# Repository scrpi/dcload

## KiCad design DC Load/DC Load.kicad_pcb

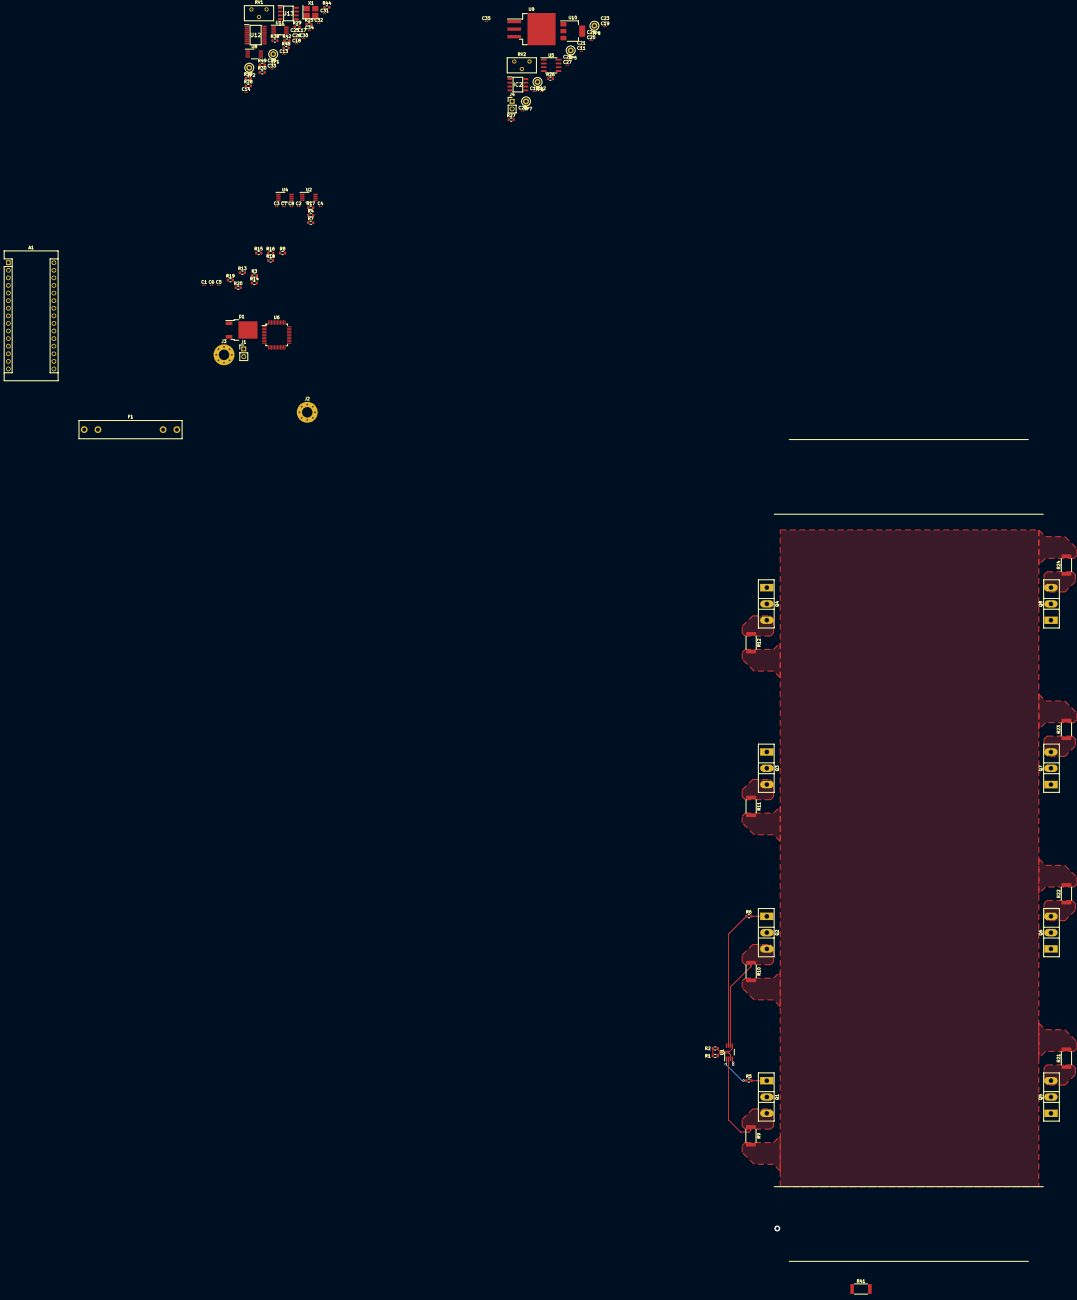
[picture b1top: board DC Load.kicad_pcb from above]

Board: 2 copper layers, 105 parts (0 on the bottom side), 62 nets.

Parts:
A1: Arduino_Nano_v3.x; Arduino_Nano
C1, C3, C5, C7, C10, C17, C20, C21, C26, C32: 1uF; C_0201_0603Metric
C2, C4, C6, C8, C13, C14, C18, C22, C23, C29, C30, C33: 0.1uF; C_0201_0603Metric
C11, C12, C24, C27, C28: 10uF; C_0201_0603Metric
C19: 470uF; C_0201_0603Metric
C25, C34, C35: 10nF; C_0201_0603Metric
C31: 0.22uF; C_0201_0603Metric
D1: V60DM100C; TO-252-2
F1: Fuse 50A; Fuseholder_Littelfuse_100_series_5x30mm
IC2: LTC1046CS8#PBF; SOIC127P599X175-8N
J1: VSENSE; PinHeader_1x02_P2.54mm_Vertical
J2: LOAD_POS; MountingHole_3.5mm_Pad_Via
J3: LOAD_NEG; MountingHole_3.5mm_Pad_Via
J4: DC 15V..18V; PinHeader_1x02_P2.54mm_Vertical
Q1, Q2, Q3, Q4, Q5, Q6, Q7, Q8: IRFP260; TO-247-3_Vertical
R1, R2, R3, R4, R13, R14, R15, R16, R42: 10K; R_0603_1608Metric
R5, R6, R7, R8, R17, R18, R19, R20: 200; R_0603_1608Metric
R9, R10, R11, R12, R21, R22, R23, R24: 0R1 1% 2W; R_2512_6332Metric
R25, R27, R28, R44: 1K; R_0603_1608Metric
R26: 470K; R_0603_1608Metric
R29, R30: 6.7K; R_0603_1608Metric
R37, R38: 1M; R_0603_1608Metric
R41: CSS2H-5930K-2L00F; R_2512_6332Metric
R48: 3K 0.05%; R_0603_1608Metric
R49: 1K 0.05%; R_0603_1608Metric
RV1: 20K; Potentiometer_Bourns_3296Y_Vertical
RV2: 10K; Potentiometer_Bourns_3296Y_Vertical
TP1: VS-; TestPoint_Loop_D2.50mm_Drill1.0mm
TP2: VS+; TestPoint_Loop_D2.50mm_Drill1.0mm
TP5: +12V; TestPoint_Loop_D2.50mm_Drill1.0mm
TP6: +3.3V; TestPoint_Loop_D2.50mm_Drill1.0mm
TP7: -5V; TestPoint_Loop_D2.50mm_Drill1.0mm
TP8: +2.048V; TestPoint_Loop_D2.50mm_Drill1.0mm
U1, U2, U4, U8: OPA2182; VSSOP-8_3.0x3.0mm_P0.65mm
U5: REF5020AID; SOIC-8_3.9x4.9mm_P1.27mm
U6: STM32F103C8Tx; LQFP-48_7x7mm_P0.5mm
U9: MC7812BD2TR4G; TO-263-3_TabPin2
U10: LD1117S33TR_SOT223; SOT-223-3_TabPin2
U11: MAX5217; MSOP-8_3x3mm_P0.65mm
U12: ADS131M02IPWR; SOP65P640X120-20N
U13: OPA277UA; SOIC127P600X175-8N
X1: FD0810004; Crystal_SMD_3225-4Pin_3.2x2.5mm_HandSoldering

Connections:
+2.048V: C11.1, RV2.3, TP8.1, U5.6 (Vout), U11.1 (REF)
+3V3: C10.1, C24.1, C25.1, C26.1, C29.1, C30.1, C32.1, C33.1, TP6.1, U5.2 (Vin), U10.2 (VO), U11.5 (~AUX), U11.7 (VDD), U12.1 (AVDD), U12.20 (DVDD), X1.1 (Vctrl), X1.4 (V+)
+12V: C1.1, C2.1, C3.1, C4.1, C5.1, C6.1, C7.1, C8.1, C12.1, C17.1, C18.1, C21.1, C22.1, C23.1, TP5.1, U1.8 (V+), U2.8 (V+), U4.8 (V+), U8.8 (V+), U9.3 (OUT), U10.3 (VI)
-3V3: C14.2, U13.4 (V-)
/ADC_DAC/ISET: U8.6 (-), U8.7
/ADC_DAC/VSENSE_N: J1.2, R37.2
/ADC_DAC/VSENSE_P: J1.1, R38.2
/MOSFETS/ISET: R1.1, R2.1, R3.1, R4.1, R13.1, R14.1, R15.1, R16.1
GND: C1.2, C2.2, C3.2, C4.2, C5.2, C6.2, C7.2, C8.2, C12.2, C13.2, C14.1, C17.2, C18.2, C19.2, C20.2, C21.2, C22.2, C23.2, C24.2, C25.2, C26.2, C28.1, C29.2, C30.2, C31.2, C32.2, C33.2, C34.2, IC2.3 (GND), J3.1, J4.2, R30.1, R41.2, R42.1, R44.2, R49.1, U1.4 (V-), U2.4 (V-), U4.4 (V-), U8.4 (V-), U9.2 (GND), U10.1 (GND), U11.2 (ADDR), U11.8 (GND), U12.2 (AGND), U12.4 (AIN0N), U12.19 (DGND), X1.2 (GND)
LOAD_NEG: R9.2, R10.2, R11.2, R12.2, R21.2, R22.2, R23.2, R24.2, R28.2, R41.1
LOAD_POS: D1.3 (A), Q1.2 (D), Q2.2 (D), Q3.2 (D), Q4.2 (D), Q5.2 (D), Q6.2 (D), Q7.2 (D), Q8.2 (D)
unnamed: C10.2, C11.2, R27.1, U5.4 (GND)
unnamed: C13.1, RV1.2, U13.7 (V+)
unnamed: C19.1, C20.1, J4.1, U9.1 (IN)
unnamed: C27.1, IC2.2 (CAP+)
unnamed: C27.2, IC2.4 (CAP-)
unnamed: C28.2, IC2.5 (VOUT), TP7.1
unnamed: C31.1, U12.18 (CAP)
unnamed: C34.1, R25.1, U12.3 (AIN0P)
unnamed: C35.1, R44.1, U12.5 (AIN1N)
unnamed: C35.2, R28.1, U12.6 (AIN1P)
unnamed: D1.1 (K), D1.2 (K), F1.1
unnamed: F1.2, J2.1
unnamed: Q1.1 (G), R5.2
unnamed: Q1.3 (S), R9.1, U1.2 (-)
unnamed: Q2.1 (G), R6.2
unnamed: Q2.3 (S), R10.1, U1.6 (-)
unnamed: Q3.1 (G), R7.2
unnamed: Q3.3 (S), R11.1, U2.2 (-)
unnamed: Q4.1 (G), R8.2
unnamed: Q4.3 (S), R12.1, U2.6 (-)
unnamed: Q5.1 (G), R17.2
unnamed: Q5.3 (S), R21.1
unnamed: Q6.1 (G), R18.2
unnamed: Q6.3 (S), R22.1
unnamed: Q7.1 (G), R19.2
unnamed: Q7.3 (S), R23.1, U4.2 (-)
unnamed: Q8.1 (G), R20.2
unnamed: Q8.3 (S), R24.1, U4.6 (-)
unnamed: R1.2, U1.3 (+)
unnamed: R2.2, U1.5 (+)
unnamed: R3.2, U2.3 (+)
unnamed: R4.2, U2.5 (+)
unnamed: R5.1, U1.1
unnamed: R6.1, U1.7
unnamed: R7.1, U2.1
unnamed: R8.1, U2.7
unnamed: R15.2, U4.3 (+)
unnamed: R16.2, U4.5 (+)
unnamed: R19.1, U4.1
unnamed: R20.1, U4.7
unnamed: R25.2, R29.1, R42.2, U13.6 (OUTPUT)
unnamed: R26.1, U5.5 (Trim/NR)
unnamed: R26.2, RV2.2
unnamed: R27.2, RV2.1
unnamed: R29.2, R37.1, TP1.1, U13.2 (-IN)
unnamed: R30.2, R38.1, TP2.1, U13.3 (+IN)
unnamed: R48.1, U11.6 (OUT)
unnamed: R48.2, R49.2, U8.5 (+)
unnamed: RV1.1, U13.8 (TRIM_2)
unnamed: RV1.3, U13.1 (TRIM_1)
unnamed: U12.17 (CLKIN), X1.3 (OUT)

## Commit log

2022-01-27 Initial commit
    Initial commit
2022-01-27 Use 8 load FETS instead of 12
    Using 8 FETS makes output resolution easier to calculate when using a power of two volatage reference in the output DAC. Also cheaper and it's easier to fit fewer devices onto the heatsink area.
2022-01-27 Bugfix - resistor in wrong spot
2022-01-27 Separate sheet for ADC and DAC
2022-01-27 Add power flags
2022-01-27 Separate sheet for power supply
2022-01-27 Add 2.048 ref
2022-01-27 Swap DAC to MAX5217
    Allows use of 2.048v ref with 3.3V VDD
2022-01-28 Swap to ADS131 ADC
2022-01-28 Assign temporary footprints
2022-01-28 Start board
